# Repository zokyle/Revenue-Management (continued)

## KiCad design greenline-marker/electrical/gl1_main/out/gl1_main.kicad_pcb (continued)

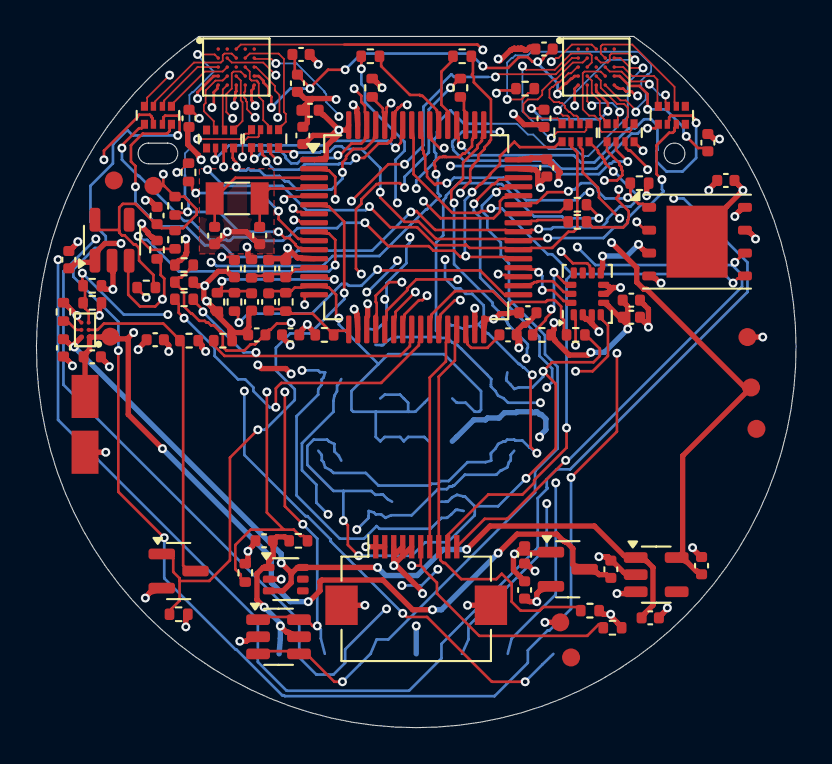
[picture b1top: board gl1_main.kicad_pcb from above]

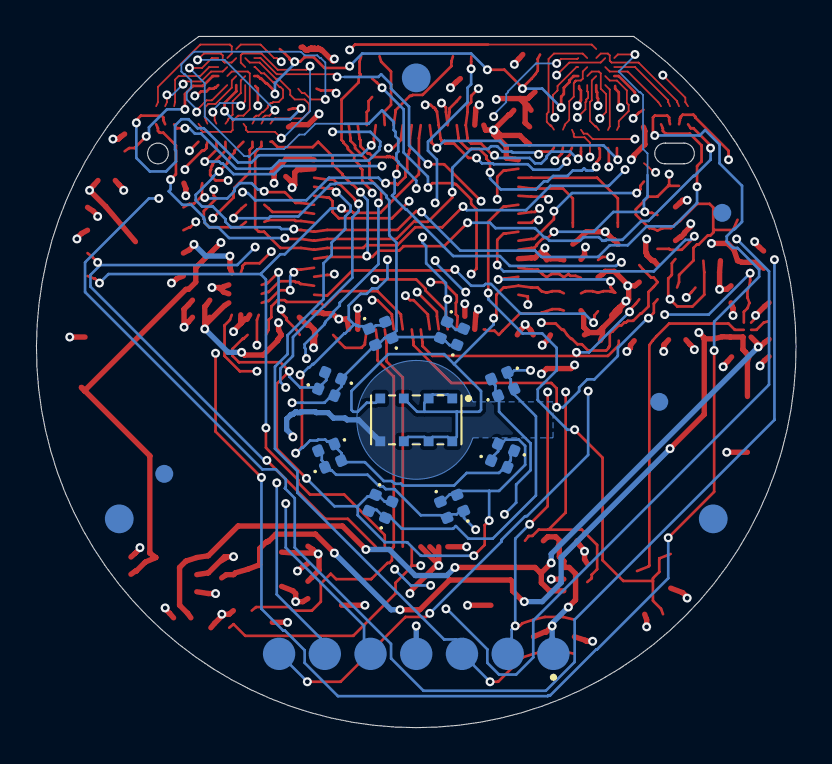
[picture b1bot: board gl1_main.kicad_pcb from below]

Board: 4 copper layers, 42.2 x 38.4 mm, 122 parts (24 on the bottom side), 95 nets.

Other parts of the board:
FID1, FID2, FID3, FID4, FID5, FID6: Fiducial; Fiducial_1mm_Mask2mm
FL1, FL2, FL3: Ball-foot land; BallFootLand_D1.6mm
H1: NPTH 1.15mm; NPTH_1.15mm

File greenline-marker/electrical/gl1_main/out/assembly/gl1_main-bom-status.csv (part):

Item,Qty,References,Value,Description,Footprint,MPN,Manufacturer,Distributor,Distributor PN,Unit Price,DNP,Status,Status note,Sourcing risk (docs/sourcing.csv),Approved alternates (docs/sourcing.csv),Sourcing row / status / checked on
1,16,C1 C2 C3 C4 C9 C10 C13 C14 C15 C17 C18 C28 C29 C30 C31 C34,100n,MLCC 0402 100 nF 16 V X7R,Capacitor_SMD:C_0402_1005Metric,GRM155R71C104KA88D,Murata,Digi-Key,490-3261-1-ND,,,PROVISIONAL,"MPN from memory, Digi-Key code from docs/SOURCING.md A17; the sourcing report records a conflicting not-recommended-for-new-designs flag","medium: stock is deep, but the life-cycle flag conflicts (not recommended for new designs at Octopart, IBS and LCSC; Active at Arrow and Future; Murata's own page not seen), and the part sits in 17 places on the two boards","Samsung CL05B104KO5NNNC (same value, voltage, dielectric and size): VERIFIED, own row",main-01 / VERIFIED / 2026-11-13
2,2,C5 C6,4u7,MLCC 0402 4.7 uF 6.3 V X5R,Capacitor_SMD:C_0402_1005Metric,GRM155R60J475ME47D,Murata,any authorised distributor (order by MPN),GRM155R60J475ME47D,,,PROVISIONAL,MPN from memory; value per DESIGN_SPEC / NETLIST_NOTES,low,"Samsung CL05A475MQ5NRNC: VERIFIED, own row",main-02 / VERIFIED / 2026-11-13
3,8,C7 C16 C19 C20 C21 C24 C25 C32,1u,MLCC 0402 1 uF 10 V X5R,Capacitor_SMD:C_0402_1005Metric,CL05A105KP5NNNC,Samsung Electro-Mechanics,any authorised distributor (order by MPN),CL05A105KP5NNNC,,,PROVISIONAL,MPN per docs/SOURCING.md action A1 (replaces the obsolete GRM155R61A105KE15D); DC-bias curve not read (A3),low,"Murata GRM155R61C105KA12D, 16 V (PROVISIONAL, own row)",replaces main-03 / VERIFIED / 2026-11-13
4,1,C8,10n,MLCC 0402 10 nF 50 V X7R,Capacitor_SMD:C_0402_1005Metric,GRM155R71H103KA88D,Murata,any authorised distributor (order by MPN),GRM155R71H103KA88D,,,PROVISIONAL,MPN from memory; value per DESIGN_SPEC / NETLIST_NOTES,low,"Samsung CL05B103KB5NNNC: VERIFIED, own row",main-04 / VERIFIED / 2026-11-13
5,2,C11 C12,6p8,MLCC 0402 6.8 pF 50 V C0G +-0.25 pF,Capacitor_SMD:C_0402_1005Metric,GRM1555C1H6R8CA01D,Murata,any authorised distributor (order by MPN),GRM1555C1H6R8CA01D,,,PROVISIONAL,MPN from memory; value per DESIGN_SPEC / NETLIST_NOTES,"low: a listing was seen, the quantity on hand was not","Yageo CC0402CRNPO9BN6R8 or KEMET C0402C689C5GACTU: both VERIFIED, own rows. Samsung CL05C6R8CB5NNNC: NOT FOUND on seven US distributor sites, do not list it",main-05 / VERIFIED / 2026-11-13
6,4,C22 C23 C26 C27,2u2,MLCC 0402 2.2 uF 10 V X5R,Capacitor_SMD:C_0402_1005Metric,GRM155R61A225KE01D,Murata,any authorised distributor (order by MPN),GRM155R61A225KE01D,,,PROVISIONAL,"MPN per docs/SOURCING.md action A2 (replaces GRM155R61A225KE95D, being discontinued; that KE01D is Murata's successor is the report's inference); DC-bias curve not read (A3)",medium: the exact reel code was out of stock at DigiKey in the one entry that was read,"Samsung CL05A225KP5NSNC (VERIFIED, own row); Murata GRT155R61A225KE01D (PROVISIONAL, own row)",replaces main-06 / VERIFIED / 2026-11-13
7,1,C33,10p,MLCC 0402 10 pF 50 V C0G 5 %,Capacitor_SMD:C_0402_1005Metric,GRM1555C1H100JA01D,Murata,any authorised distributor (order by MPN),GRM1555C1H100JA01D,,,PROVISIONAL,MPN from memory; value per DESIGN_SPEC / NETLIST_NOTES,low,"Samsung CL05C100JB5NNNC: VERIFIED, own row. Murata GRM1555C1H100FA01D (1 %) is DigiKey's suggested upgrade (not checked)",main-07 / VERIFIED / 2026-11-13
8,8,D1 D3 D5 D7 D9 D11 D13 D15,LED red,LED super red 631 nm 0402,LED_SMD:LED_0402_1005Metric,VLMS1500-GS08,Vishay,any authorised distributor (order by MPN),VLMS1500-GS08,,,PROVISIONAL,"MPN research-confirmed; land pattern is the generic KiCad 0402 LED, polarity mark and pad sizes not checked","low: a common part. 1000 markers need 8,000, more than the DigiKey figure; Mouser's covers it","Kingbright APHHS1005SURCK (carried from rev 2, not searched today: PROVISIONAL)",main-08 / VERIFIED / 2026-11-13
9,8,D2 D4 D6 D8 D10 D12 D14 D16,LED NIR,LED 850 nm 0402 (alternative: Inolux IN-S42CTQIR),LED_SMD:LED_0402_1005Metric,SFH 4053B,ams OSRAM,any authorised distributor (order by MPN),SFH 4053B,,,PROVISIONAL,"MPN from DESIGN_SPEC E3 (successor of the SFH 4053; its data sheet has not been read); land pattern is the generic KiCad 0402 LED, polarity mark and pad sizes not checked","medium to high: one US distributor with stock, and the life-cycle evidence conflicts (maker's page: full production; RS: 'currently unavailable' and 'being discontinued by the manufacturer')","Inolux IN-S42CTQIR, the alternative named in the design: VERIFIED at DigiKey, own row; dimmer (5.5 against 9 mW/sr typical at 70 mA)",main-09 / VERIFIED / 2026-11-13
10,1,J1,LCD FPC 10,"FPC connector 10 x 0.5 mm, TOP contact, 2.0 mm high; PIN-1 EDGE OF THE TAIL PROVISIONAL (tail pin n on pad 11 - n)",Connector_FFC-FPC:Hirose_FH12-10S-0.5SH_1x10-1MP_P0.50mm_Horizontal,FH12A-10S-0.5SH(55),Hirose,Digi-Key,HFK110CT-ND,,,PROVISIONAL,"top-contact FH12A on the bottom-contact FH12 land pattern (spec); pin order and pin-1 edge of the tail PROVISIONAL (LCD_TAIL, LCD_TAIL_PIN1_EDGE); placed per spec E24 (mouth at y -17.30), which overrides the YAML point; Digi-Key PN from docs/sourcing.csv","low for supply. Design risk: the footprint named in the BOM is the bottom-contact FH12 land pattern, and no extract confirmed that the top-contact FH12A fits it","Same part at Future and Heilind. No drop-in from another maker was searched. Fallback named by amendment E24 if the fold of the display's tail does not fit: a 1.0 mm high back-flip connector about 3.5 mm deep, 'Hirose FH34SRJ-10S-0.5SH class' (not searched: PROVISIONAL; a shallower connector, so a different land pattern)",main-11 / VERIFIED / 2026-11-13
11,1,PD1,VEMD8080,"PIN photodiode 4.5 mm2, 350-1100 nm; LAND PATTERN PROVISIONAL",gleda:VEMD8080_4.8x2.5mm_PROVISIONAL,VEMD8080,Vishay,any authorised distributor (order by MPN),VEMD8080,,,PROVISIONAL,"package research-confirmed; pad layout and anode pad from public footprints, not the Vishay drawing (VEMD8080_PADS)",low,Sister part VEMD8081 (DigiKey link seen; fit not checked: PROVISIONAL),main-12 / VERIFIED / 2026-11-13
12,1,Q1,BSS138,"N-MOSFET 50 V, VGS(th) 1.5 V max, SOT-23 (pulls the charger's TS input low)",Package_TO_SOT_SMD:SOT-23,BSS138LT1G,onsemi,Digi-Key,product page 918376 (SKU not seen),,,PROVISIONAL,"part named in DESIGN_SPEC; order code from docs/sourcing.csv; pin order (G1 S2 D3), threshold and leakage from memory",low,Same part at Arrow and Mouser,main-13 / VERIFIED / 2026-11-13
13,1,R1,10R,Resistor 0402 1 % 10R,Resistor_SMD:R_0402_1005Metric,RC0402FR-0710RL,Yageo,any authorised distributor (order by MPN),RC0402FR-0710RL,,,PROVISIONAL,MPN from memory; value per DESIGN_SPEC / NETLIST_NOTES,"low: one per marker, several distributors",Panasonic ERJ-2RKF10R0X (a Mouser page title only: PROVISIONAL),main-14 / VERIFIED / 2026-11-13
14,2,R2 R19,10k,Resistor 0402 1 % 10k,Resistor_SMD:R_0402_1005Metric,RC0402FR-0710KL,Yageo,any authorised distributor (order by MPN),RC0402FR-0710KL,,,PROVISIONAL,MPN from memory; value per DESIGN_SPEC / NETLIST_NOTES,low,"Panasonic ERJ-2RKF1002X: VERIFIED, own row",main-15 / VERIFIED / 2026-11-13
15,11,R3 R10 R12 R13 R15 R16 R20 R21 R22 R29 R30,100k,Resistor 0402 1 % 100k,Resistor_SMD:R_0402_1005Metric,RC0402FR-07100KL,Yageo,any authorised distributor (order by MPN),RC0402FR-07100KL,,,PROVISIONAL,MPN from memory; value per DESIGN_SPEC / NETLIST_NOTES,low,"Panasonic ERJ-2RKF1003X: VERIFIED, own row",main-16 / VERIFIED / 2026-11-13
16,2,R4 R5,1k,Resistor 0402 1 % 1k,Resistor_SMD:R_0402_1005Metric,RC0402FR-071KL,Yageo,any authorised distributor (order by MPN),RC0402FR-071KL,,,PROVISIONAL,MPN from memory; value per DESIGN_SPEC / NETLIST_NOTES,low,"Panasonic ERJ-2RKF1001X (from memory, not searched: PROVISIONAL)",main-17 / VERIFIED / 2026-11-13
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
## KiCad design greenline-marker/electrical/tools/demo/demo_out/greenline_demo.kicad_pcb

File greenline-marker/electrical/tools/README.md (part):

# gleda - GreenLine scripted EDA toolchain

`gleda` turns a "netlist as code" design description (Python) into a verified
KiCad 7 board.  KiCad's own DRC is the judge; nothing is reported as passing
unless KiCad says so.

The flow, each step a module that can be used on its own:

```
design script (Python)  ->  checks  ->  board  ->  router  ->  zone fill + KiCad DRC
                                                                     |
                 schematic + netlist round trip   <-   outputs (Gerber, drill, BOM,
                                                       pick-and-place, renders, JSON)
```

This file documents the design model, the checks, footprints, the board
builder, the DRC runner, the **router**, the **outputs**, the **schematic
generator** and the **demo build**, each with its limits.  Two sections are
written to be read on their own: **[Quick start: authoring a new
design](#quick-start-authoring-a-new-design)** and
**[Limitations](#limitations)** (everything the toolchain does not do, in one
place).

```
tools/
  gleda/
    model.py       design description (pure Python, no pcbnew)
    coords.py      THE design <-> KiCad coordinate conversion
    geometry.py    outline paths/polygons, placed pads, courtyards (shapely)
    footprints.py  programmatic footprints + KiCad library wrappers
    checks.py      ERC-style and placement checks
    board.py       .kicad_pcb / .kicad_pro / .kicad_dru generation, routing
                   primitives in/out, via tenting
    drc.py         zone fill + KiCad DRC + report parser + pass/fail policy
    kicad_cli.py   kicad-cli wrapper, SVG export, SVG reader
    router.py      autorouter (escape stage, negotiated routing, end game,
                   cleanup, exact audit, plane-fill prediction)
    raster.py      routing grid and exact obstacle rasterisation
    _astar.py      A* search kernel (numba-compiled when numba is installed)
    routeplot.py   quick matplotlib picture of a routed design (debug aid)
    outputs.py     Gerbers, drill, pick-and-place, BOM, netlist / mechanical JSON,
                   renders, fab README + zip - each checked against the model
    schematic.py   KiCad 7 schematic (one sheet per group), PDF, netlist round trip
  demo/
    quickstart_board.py  the smallest complete design + the whole flow (start here)
    demo_design.py     the GreenLine DEMO board (stand-in for the real GL-1)
    build_demo.py      checks -> board -> route -> DRC -> outputs -> schematic
    demo_out/          everything the last demo build produced
  tests/           pytest suite (run it from tools/)
    mini_design.py     round 30 mm fixture (castellated module, cutout, notch, slot)
    dshape_design.py   GreenLine-shaped fixture (D outline, LQFP-64, two BGAs,
                       bottom LED ring + contact row, fine net class)
    proof_core.py      builds both, KiCad DRC, plots, orientation proof
    proof_out/         outputs of the last proof run
```

## Requirements

KiCad 7.0.x with its Python module.  Always use the system interpreter:

```
cd electrical/tools
/usr/bin/python3 -m pytest -q            # test suite (about 2 minutes)
/usr/bin/python3 -m pytest -q --runslow  # ... plus the demo build from nothing (5 to 6 minutes in all)
/usr/bin/python3 demo/build_demo.py      # the whole flow on the demo board, exit 0 only if
                                         # checks, routing, KiCad DRC and round trip all pass
/usr/bin/python3 tests/proof_core.py     # build + DRC + render both reference boards
/usr/bin/python3 -m gleda.drc out/board.kicad_pcb [--allow-unconnected]
```

`pdftoppm` / `pdfinfo` (poppler-utils) turn KiCad's PDF plots into PNGs; numba
makes the router usable on real boards.  No GUI is ever started and nothing
is downloaded.

## The whole flow in one script

```python
import sys; sys.path.insert(0, "electrical/tools")
from gleda import checks, board, router, drc, outputs, schematic

design = my_design()                                    # a gleda.model.Design, see below

checks.run_checks(design).raise_if_errors()             # ERC-style + placement checks
files = board.build_board(design, "out")                # .kicad_pcb / .kicad_pro / .kicad_dru
result = router.route(design)                           # RouteResult; .complete, .unrouted
board.apply_routing(files.pcb, result.tracks, result.vias, via_tenting=design.via_tenting)
res = drc.run_drc(files.pcb, json_path="out/drc.json")  # zone fill + KiCad DRC
drc.assert_clean(res)                                   # 0 errors, 0 unconnected - or DrcError
package = outputs.generate_outputs(design, files.pcb, "out", drc_result=res, vias=result.vias)
assert package.ok, package.problems                     # plotted data == design model
sch = schematic.generate_schematic(design, "out")       # <name>.kicad_sch + one sheet per group
schematic.export_pdf(sch.root, "out/schematic.pdf")
trip = schematic.round_trip(design, sch.root)           # KiCad's netlist vs the model
assert trip.ok, trip.problems
```

`demo/build_demo.py` is exactly this with reporting around it.

## Quick start: authoring a new design

A design is one Python function that returns a `gleda.model.Design`; a second
short function takes it through the flow.  **Start from
`demo/quickstart_board.py`**: 135 lines, one 16-ball 0.5 mm BGA with its
capacitor, a pull-up and a contact row on a 24 mm D-shaped board, every step
below in the order one writes it, and a `build(design, out)` function that is
the whole flow with honest exit codes.  The test suite runs it, so it works as
written:

```
cd electrical/tools
/usr/bin/python3 demo/quickstart_board.py /some/empty/dir     # about 10 s
#   gleda checks for quickstart: 0 error(s), 0 warning(s)
#   routed 16/16 connections (100.0 %) of 10 nets, 102 tracks, 16 vias, 126.6 mm, 0 audit violation(s)
#   KiCad DRC: 0 error(s), 0 unconnected, 0 warning(s)
#   outputs: 34 files, 0 problem(s) against the model
#   netlist round trip matches: 10 nets, 26 pads, 4 components, 4 unconnected pins
```

`demo/demo_design.py` and `demo/build_demo.py` are the same thing at the size
of the real board (100 parts), with stage reporting around it.

1. **Outline and rules.**  `Outline(PathShape.d_shape(r, flat_y))` (or
   `Circle`, `RoundedPolygon`, any line + arc `PathShape`), then
   `add_hole` / `add_npth_slot` / `add_cutout`.  `Design(name, outline,
   layers=4, rules=US_4L_STD, board_thickness=0.8)`; use `US_4L_FINE` (board
   minimums 0.09 / 0.09 mm) only if a fine-pitch BGA forces it.
2. **Net classes.**  `Default` (0.15 / 0.127) and `Power` (0.30 / 0.127)
   exist.  Add `d.add_netclass("Fine", track_width=0.09, clearance=0.09)` for
   the nets on the inner balls of a 0.5 mm BGA and **declare where it may be
   fine**: `d.add_fine_area("U2", margin=5.0)`.  Outside the fine areas those
   nets are routed and DRC-checked at the standard 0.15 / 0.127 mm.  Try this
   first; if the router cannot finish that way (it cannot on the demo board),
   remove the fine areas - the fine tracks may then run anywhere on those
   nets, the checks warn, the router widens what it can, and the fab README
   tells the fab to quote the whole board at 0.09 / 0.09 mm.
3. **Parts.**  `d.add(Part(ref, value, footprint, pins=..., mpn=...,
   manufacturer=..., distributor=..., distributor_pn=..., unit_price=...,
   x=..., y=..., rotation=..., side="top" | "bottom", height_mm=...,
   group="sheet name"))`.  `footprint` is a KiCad `"Lib:Name"` string or a
   generator from `gleda.footprints` (`bga`, `quad_package`, `two_pad`,
   `pad_row`, `test_pad`, `battery_tab`, `fpc_connector`,
   `castellated_module` ...).  `pins` maps pin name -> pad number(s) and
   electrical type.  Bare pads and tabs get `in_bom=False`.
4. **Nets.**  `d.net("NAME", "U1.PA5", "R3.1", netclass="Power")`; every pin
   must be on a net, be of type `nc` or be listed in `d.no_connect(...)`.
   Supplies fed from outside the netlist get `power_flag=True`.
5. **Planes, keep-outs, mechanics.**  `d.add_plane("GND", "In1.Cu")`,
   `d.add_plane("V2V8", "In2.Cu", routable=True)` (plane and third routing
   layer), `d.add_body_keepout("U4")` (no copper under a MEMS body),
   `d.add_keepout(shape, layers=..., tracks=..., vias=..., copper=...,
   footprints=...)` (for example `tracks=False, vias=True` over a wetted
   area: no via holes there), `d.add_placement_keepout`, `d.add_height_limit`.
6. **Fab and assembly details.**  `d.via_tenting = "bottom"`,
   `d.via_protection = "plugged from the bottom side (IPC-4761 type III-a)"`,
   `d.fab_notes.append("...")`, three `d.add_fiducial(x, y, side=...)` per
   assembled side.
7. **Run the checks until they are clean**: `print(checks.run_checks(d).text())`.
   Errors stop the flow; read the warnings (`fine_unconfined`, `no_fiducials`,
   `plane_partial`, `decoupling_far` ...).
8. **Build, route, judge, export** - the script under "The whole flow in one
   script" above.  The router's result is honest (`result.complete`,
   `result.unrouted`, `result.warnings`); KiCad's DRC decides
   (`drc.assert_clean`); `outputs.generate_outputs` refuses a board that is
   not clean and verifies what it plotted against the model.

What makes a board routable by THIS router (learned on the demo, see the end
of this file): pins of a fixed-function part on the side that faces their
destination; about 1.4 x 2.0 mm per 0402 that needs a plane via; the sides of
a BGA that face the rest of the circuit kept clear for the bus escape; nothing
in the pocket between a hole and the next part; fiducials and fine areas
placed before routing (both take routing room).

**The first mistake everybody makes**: an inner ball of a 0.5 mm-pitch BGA on
a net whose class is wider than 0.09 mm (`Default`, `Power`).  Only a 0.09 mm
track with 0.09 mm clearance passes between two 0.23 mm balls, a via does not
fit between them and vias are never put in pads - so such a ball cannot be
reached, whatever net it is on, GND included.  Put every net that touches an
inner ball into a fine class (the demo: `Fine` for signals, `CamPower`
0.15 / 0.09 for supply balls on the outer ring), give the BGA pads
`pad_clearance=0.09`, and keep supplies on the outer ring where the ball map
lets you.  The router does not hang on it and does not pretend:

```
routed 15/16 connections (93.8 %) of 10 nets, 83 tracks, 15 vias, ...
OPEN D0: [['J1.3'], ['U1.B2']]  [no path from U1.B2 to J1.3]
```

A net the router leaves open is always reported like this
(`result.unrouted` -> `Unrouted.net`, `.pieces`, `.reason`; per connection in
`result.failures`) and `result.complete` is False.  Move a part or a pin,
change the class, and run again - or route that net by hand in KiCad and mark
it `no_route=True`.

## Conventions (read this first)

* Units are millimetres.  The design origin is the **board centre** (for the
  D-shaped board: the centre of the circle), **+x is right, +y is up** as seen
  from the top of the board; rotation is counter-clockwise positive.
* KiCad's y axis points down.  The conversion happens in exactly one module,
  `gleda/coords.py` (`to_kicad_mm`, `from_kicad_mm`, ...).  The board centre is
  placed at (100, 100) mm on the KiCad page and the board's auxiliary
  (drill/place) origin is set to the same point.
* Footprint-local coordinates (custom footprints, `FootprintGeom`) use the
  same handedness: +y up, looking at the component side.
* **Bottom-side parts** follow KiCad's native definition, so `Part.rotation`
  is the number KiCad stores, shows and writes to position files:
  the footprint is flipped about its local X axis and then rotated CCW as
  seen from the top:

      top:     board = (x, y) + R(rotation) . (lx,  ly)
      bottom:  board = (x, y) + R(rotation) . (lx, -ly)

  `coords.local_to_board()` implements this and
  `tests/test_board.py::test_pads_match_model_geometry` proves that every pad
  position predicted by the model equals what pcbnew reports for the saved
  board.  `tests/test_board.py::test_top_view_svg_has_plus_y_up` proves from a
  KiCad SVG plot that a part placed at +y is drawn toward the top.

## Describing a design

```python
from gleda.model import (Design, Outline, Circle, RoundedPolygon, PathShape, Part,
                         two_pin, n_pin, US_4L_FINE, BOTTOM)
from gleda import footprints as F

# circle r = 21.2 mm about the origin, clipped by the chord y = +17.3 mm
outline = Outline(PathShape.d_shape(21.2, 17.3))
# also: Outline(Circle(0, 0, 19.0)), RoundedPolygon(...), any line + arc path:
#   PathShape.begin(-5, 0).line_to(5, 0).arc_to(-5, 0, 0, 0, ccw=True).close()
#   PathShape.clipped_circle(0, 0, 21.2, [(90, 17.3), (270, 19.0)])
outline.add_cutout(Circle(9.0, 0.0, 6.5))              # internal routed cutout
outline.add_notch(RoundedPolygon.rect(0, -21.2, 3, 2, 0.4))   # crosses the edge
outline.add_slot(-6, -11, -4, -11, 0.8)
outline.add_hole(-12, 5, 1.2)                          # NPTH

d = Design("greenline", outline, layers=4, rules=US_4L_FINE, board_thickness=0.8)
d.add_netclass("Fine", track_width=0.09, clearance=0.09)   # BGA escape only
d.via_tenting = "bottom"                               # "both" (default) | "bottom" | "top" | "none"
d.via_protection = "plugged from the bottom side (IPC-4761 type III-a)"   # -> fab README
d.fab_notes.append("The bottom side is a wetted surface: no open via holes there.")

cam = F.bga("Cam_BGA25", 5, 5, pitch=0.5, pad_d=0.23, body=(3.47, 2.95), height=2.76,
            pad_clearance=0.09, courtyard_margin=0.2)
d.add(Part("U2", "Camera", cam,
           pins={"D0": ("B2", "bidir"), "AVDD": ("C5", "power_in"),
                 "GND": (("E2", "E3", "E4"), "power_in"), "NC": ("A1", "nc")},  # ... all balls
           mpn="...", manufacturer="...", distributor="Digi-Key", distributor_pn="...",
           unit_price=6.0, x=-10.2, y=15.6, rotation=0, side="top", height_mm=2.76,
           group="camera"))
d.add(Part("C1", "100n", "Capacitor_SMD:C_0402_1005Metric", pins=two_pin(),
           mpn="...", x=-7.2, y=15.3, rotation=90, group="camera"))
d.add(Part("J2", "Cradle pads", F.pad_row("ContactRow", 7, 2.54, 1.8), pins=n_pin(7),
           x=0, y=-17.0, side=BOTTOM, in_bom=False))    # bare pads on the bottom

d.net("GND", "U2.GND", "C1.2", "J2.4", netclass="Power")
d.net("V2V8", "U2.AVDD", "C1.1", netclass="Power", power_flag=True)
d.net("CAM_D0", "U2.D0", "U1.PC6", netclass="Fine")    # inner ball: fine class
d.no_connect("U1.P0.13")                               # pin names may contain dots

d.add_plane("GND", "In1.Cu")
d.add_plane("+3V0", "In2.Cu")
d.add_body_keepout("U4")                               # no copper on F.Cu under the IMU body
d.add_keepout(RoundedPolygon.rect(0, -5.2, 34, 10), layers=("F.Cu",), name="battery",
              tracks=False, vias=False, copper=False, footprints=True)   # placement only
d.add_fine_area("U2", margin=5.0)                      # Fine may be fine only around U2
d.add_fiducial(-19.3, -0.8)                            # FID1, top; three per assembled side
d.add_fiducial(-13.5, -3.0, side=BOTTOM)
```

Pin shorthand accepted by `Part(pins=...)`: `"5"`, `("5", "input")`,
`(("6", "7"), "power_in")`, `["6", "7"]` or a `Pin` object.  Electrical types:
`power_in, power_out, passive, input, output, bidir, open_drain, nc`.
`pins=None` means a two-pin passive (`two_pin()`).

Per-net router options live on `Net`: `width`, `max_vias`, `layers`,
`no_route`, `priority`; `power_flag=True` marks a supply that is driven from
outside the netlist (battery tab, connector).

Tri-state outputs that share a line (camera bus, SPI MISO) must be typed
`bidir`: two `output` pins on one net are an `output_conflict` error.

### Rule set

`gleda.model.Rules` is a frozen parameter object; the default instance is
`US_4L_STD`:

| rule | `US_4L_STD` | `US_4L_FINE` |
|------|-------------|--------------|
| board minimum track / clearance | 0.127 mm / 0.127 mm | **0.09 mm / 0.09 mm** |
| via (through only) | 0.50 mm pad / 0.25 mm drill | same |
| min annular ring | 0.125 mm | same |
| hole to hole | 0.25 mm | same |
| hole wall to foreign copper | 0.20 mm | same |
| copper to board edge | 0.30 mm | same |
| default / power track | 0.15 mm / 0.30 mm | same |
| default clearance (classes Default, Power) | 0.127 mm | same |
| zone clearance / min width | 0.20 mm / 0.15 mm | same |

Use `dataclasses.replace(US_4L_STD, name="...", ...)` for another fab and pass
it to `Design(rules=...)`.

### Net classes: own track width and clearance

`Design` creates `Default` (0.15 / 0.127) and `Power` (0.30 / 0.127) from the
rules; `Design.add_netclass(name, track_width, clearance, via_diameter,
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
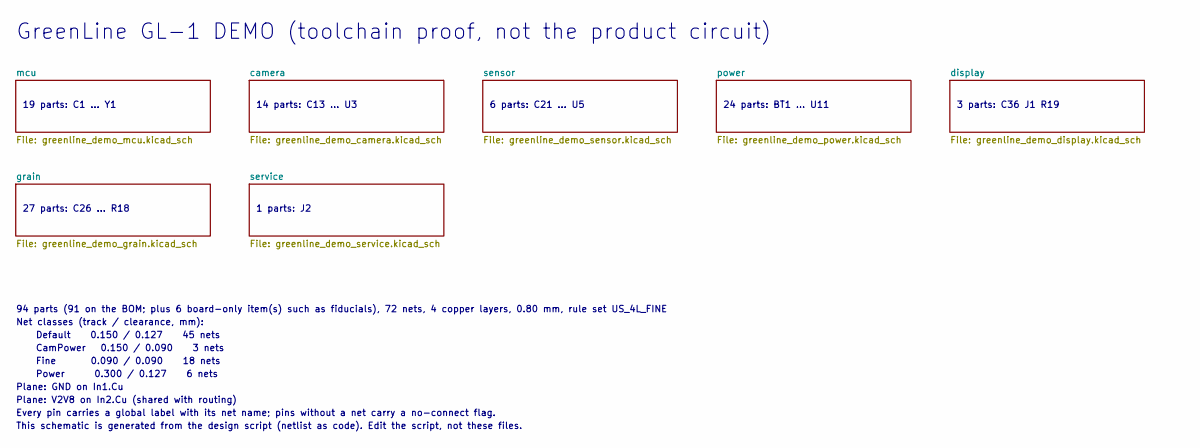
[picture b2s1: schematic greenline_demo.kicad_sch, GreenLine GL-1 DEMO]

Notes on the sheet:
GreenLine GL-1 DEMO (toolchain proof, not the product circuit)
19 parts: C1 ... Y1
14 parts: C13 ... U3
6 parts: C21 ... U5
24 parts: BT1 ... U11
3 parts: C36 J1 R19
27 parts: C26 ... R18
1 parts: J2
94 parts (91 on the BOM; plus 6 board-only item(s) such as fiducials), 72 nets, 4 copper layers, 0.80 mm, rule set US_4L_FINE
Net classes (track / clearance, mm):
Default 0.150 / 0.127 45 nets
CamPower 0.150 / 0.090 3 nets
Fine 0.090 / 0.090 18 nets
Power 0.300 / 0.127 6 nets
Plane: GND on In1.Cu
Plane: V2V8 on In2.Cu (shared with routing)
Every pin carries a global label with its net name; pins without a net carry a no-connect flag.
This schematic is generated from the design script (netlist as code). Edit the script, not these files.

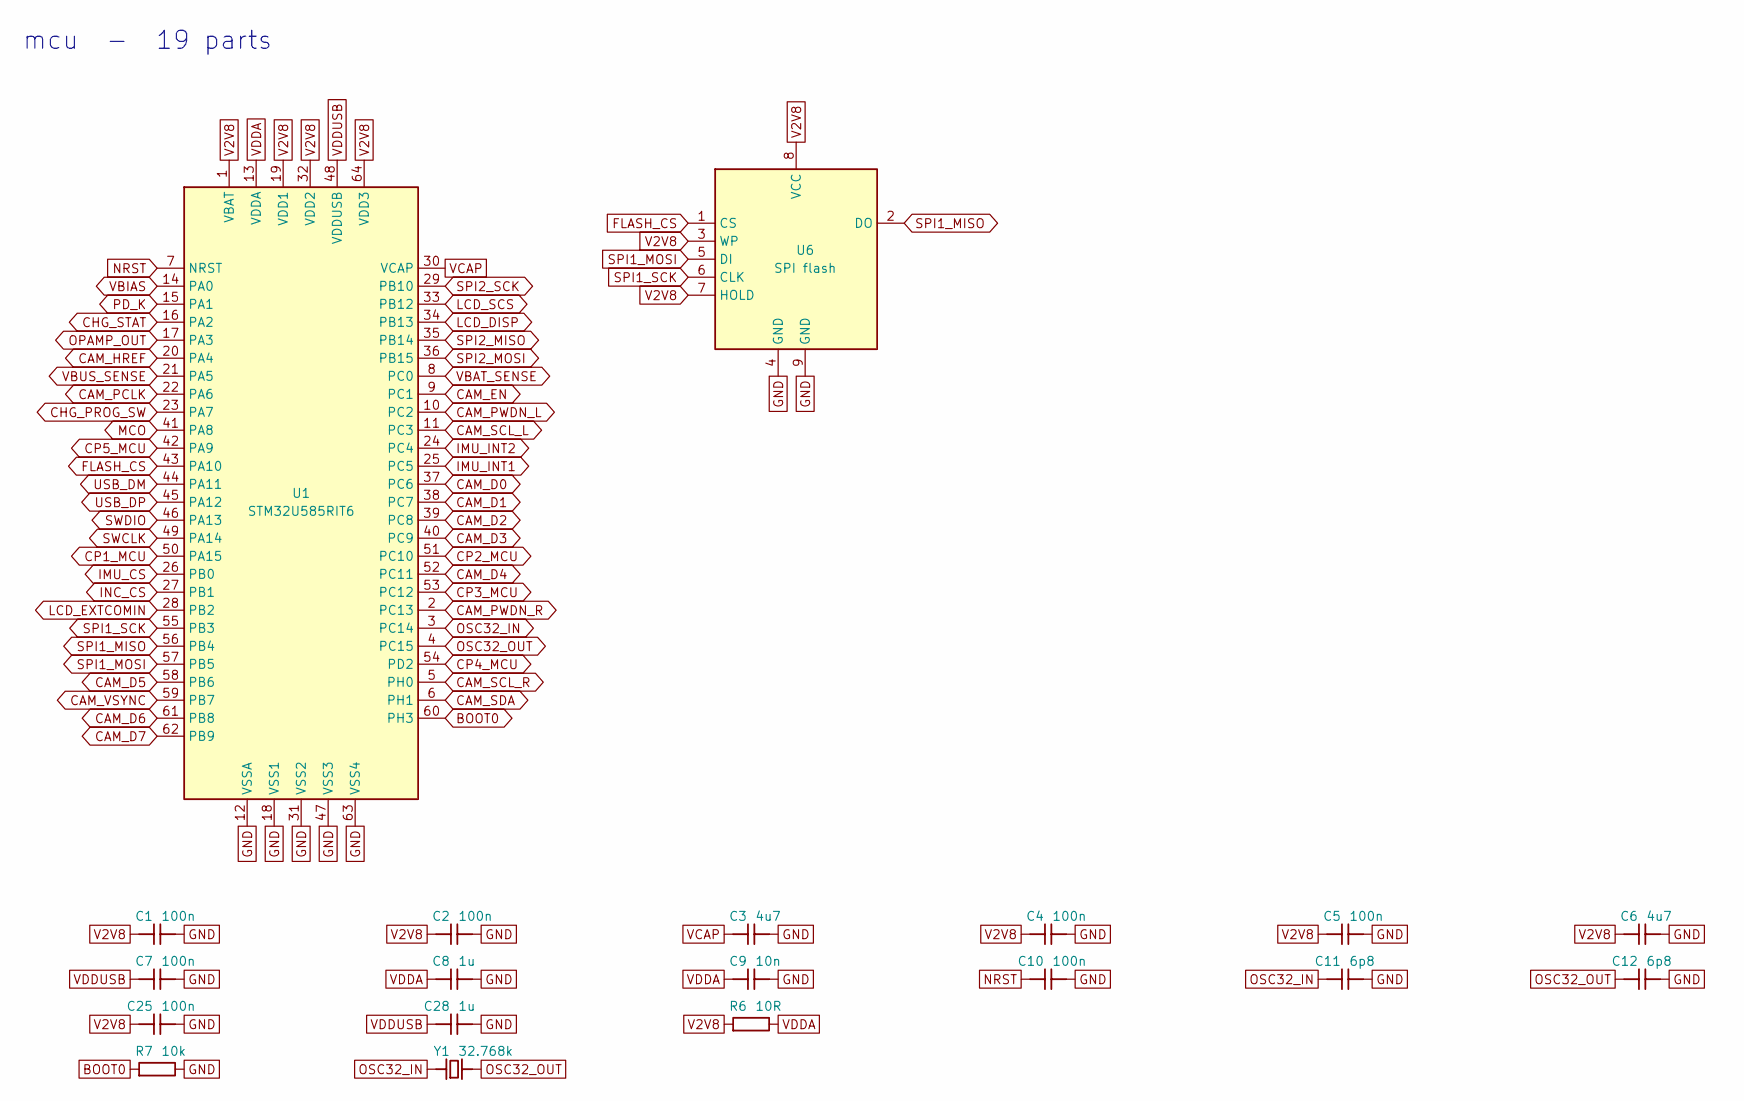
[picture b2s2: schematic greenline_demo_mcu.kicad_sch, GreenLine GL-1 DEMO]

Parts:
C1, C2, C4, C5, C7, C10, C25: 100n; C_0402_1005Metric; MPN GRM155R71C104KA88D
C3, C6: 4u7; C_0402_1005Metric; MPN GRM155R60J475ME47D
C8, C28: 1u; C_0402_1005Metric; MPN GRM155R61A105KE15D
C9: 10n; C_0402_1005Metric; MPN GRM155R71H103KA88D
C11, C12: 6p8; C_0402_1005Metric; MPN GRM1555C1H6R8CA01D
R6: 10R; R_0402_1005Metric; MPN RC0402FR-0710RL
R7: 10k; R_0402_1005Metric; MPN RC0402FR-0710KL
U1: STM32U585RIT6; LQFP-64_10x10mm_P0.5mm; MPN STM32U585RIT6
U6: SPI flash; WSON-8-1EP_6x5mm_P1.27mm_EP3.4x4.3mm; MPN MX25R6435FZNIL0
Y1: 32.768k; Crystal_SMD_3215-2Pin_3.2x1.5mm; MPN ABS07-120-32.768KHZ-T

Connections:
BOOT0: R7.1, U1.60 (PH3)
CAM_D0: U1.37 (PC6); also elsewhere on the board
CAM_D1: U1.38 (PC7); also elsewhere on the board
CAM_D2: U1.39 (PC8); also elsewhere on the board
CAM_D3: U1.40 (PC9); also elsewhere on the board
CAM_D4: U1.52 (PC11); also elsewhere on the board
CAM_D5: U1.58 (PB6); also elsewhere on the board
CAM_D6: U1.61 (PB8); also elsewhere on the board
CAM_D7: U1.62 (PB9); also elsewhere on the board
CAM_EN: U1.9 (PC1); also elsewhere on the board
CAM_HREF: U1.20 (PA4); also elsewhere on the board
CAM_PCLK: U1.22 (PA6); also elsewhere on the board
CAM_PWDN_L: U1.10 (PC2); also elsewhere on the board
CAM_PWDN_R: U1.2 (PC13); also elsewhere on the board
CAM_SCL_L: U1.11 (PC3); also elsewhere on the board
CAM_SCL_R: U1.5 (PH0); also elsewhere on the board
CAM_SDA: U1.6 (PH1); also elsewhere on the board
CAM_VSYNC: U1.59 (PB7); also elsewhere on the board
CHG_PROG_SW: U1.23 (PA7); also elsewhere on the board
CHG_STAT: U1.16 (PA2); also elsewhere on the board
CP1_MCU: U1.50 (PA15); also elsewhere on the board
CP2_MCU: U1.51 (PC10); also elsewhere on the board
CP3_MCU: U1.53 (PC12); also elsewhere on the board
CP4_MCU: U1.54 (PD2); also elsewhere on the board
CP5_MCU: U1.42 (PA9); also elsewhere on the board
FLASH_CS: U1.43 (PA10), U6.1 (CS)
GND: C1.2, C2.2, C3.2, C4.2, C5.2, C6.2, C7.2, C8.2, C9.2, C10.2, C11.2, C12.2, C25.2, C28.2, R7.2, U1.12 (VSSA), U1.18 (VSS1), U1.31 (VSS2), U1.47 (VSS3), U1.63 (VSS4), U6.4 (GND), U6.9 (GND); also elsewhere on the board
IMU_CS: U1.26 (PB0); also elsewhere on the board
IMU_INT1: U1.25 (PC5); also elsewhere on the board
IMU_INT2: U1.24 (PC4); also elsewhere on the board
INC_CS: U1.27 (PB1); also elsewhere on the board
LCD_DISP: U1.34 (PB13); also elsewhere on the board
LCD_EXTCOMIN: U1.28 (PB2); also elsewhere on the board
LCD_SCS: U1.33 (PB12); also elsewhere on the board
MCO: U1.41 (PA8); also elsewhere on the board
NRST: C10.1, U1.7 (NRST); also elsewhere on the board
OPAMP_OUT: U1.17 (PA3); also elsewhere on the board
OSC32_IN: C11.1, U1.3 (PC14), Y1.1
OSC32_OUT: C12.1, U1.4 (PC15), Y1.2
PD_K: U1.15 (PA1); also elsewhere on the board
SPI1_MISO: U1.56 (PB4), U6.2 (DO)
SPI1_MOSI: U1.57 (PB5), U6.5 (DI); also elsewhere on the board
SPI1_SCK: U1.55 (PB3), U6.6 (CLK); also elsewhere on the board
SPI2_MISO: U1.35 (PB14); also elsewhere on the board
SPI2_MOSI: U1.36 (PB15); also elsewhere on the board
SPI2_SCK: U1.29 (PB10); also elsewhere on the board
SWCLK: U1.49 (PA14); also elsewhere on the board
SWDIO: U1.46 (PA13); also elsewhere on the board
USB_DM: U1.44 (PA11); also elsewhere on the board
USB_DP: U1.45 (PA12); also elsewhere on the board
V2V8: C1.1, C2.1, C4.1, C5.1, C6.1, C25.1, R6.1, U1.1 (VBAT), U1.19 (VDD1), U1.32 (VDD2), U1.64 (VDD3), U6.3 (WP), U6.7 (HOLD), U6.8 (VCC); also elsewhere on the board
VBAT_SENSE: U1.8 (PC0); also elsewhere on the board
VBIAS: U1.14 (PA0); also elsewhere on the board
VBUS_SENSE: U1.21 (PA5); also elsewhere on the board
VCAP: C3.1, U1.30 (VCAP)
VDDA: C8.1, C9.1, R6.2, U1.13 (VDDA)
VDDUSB: C7.1, C28.1, U1.48 (VDDUSB); also elsewhere on the board

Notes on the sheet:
mcu - 19 parts

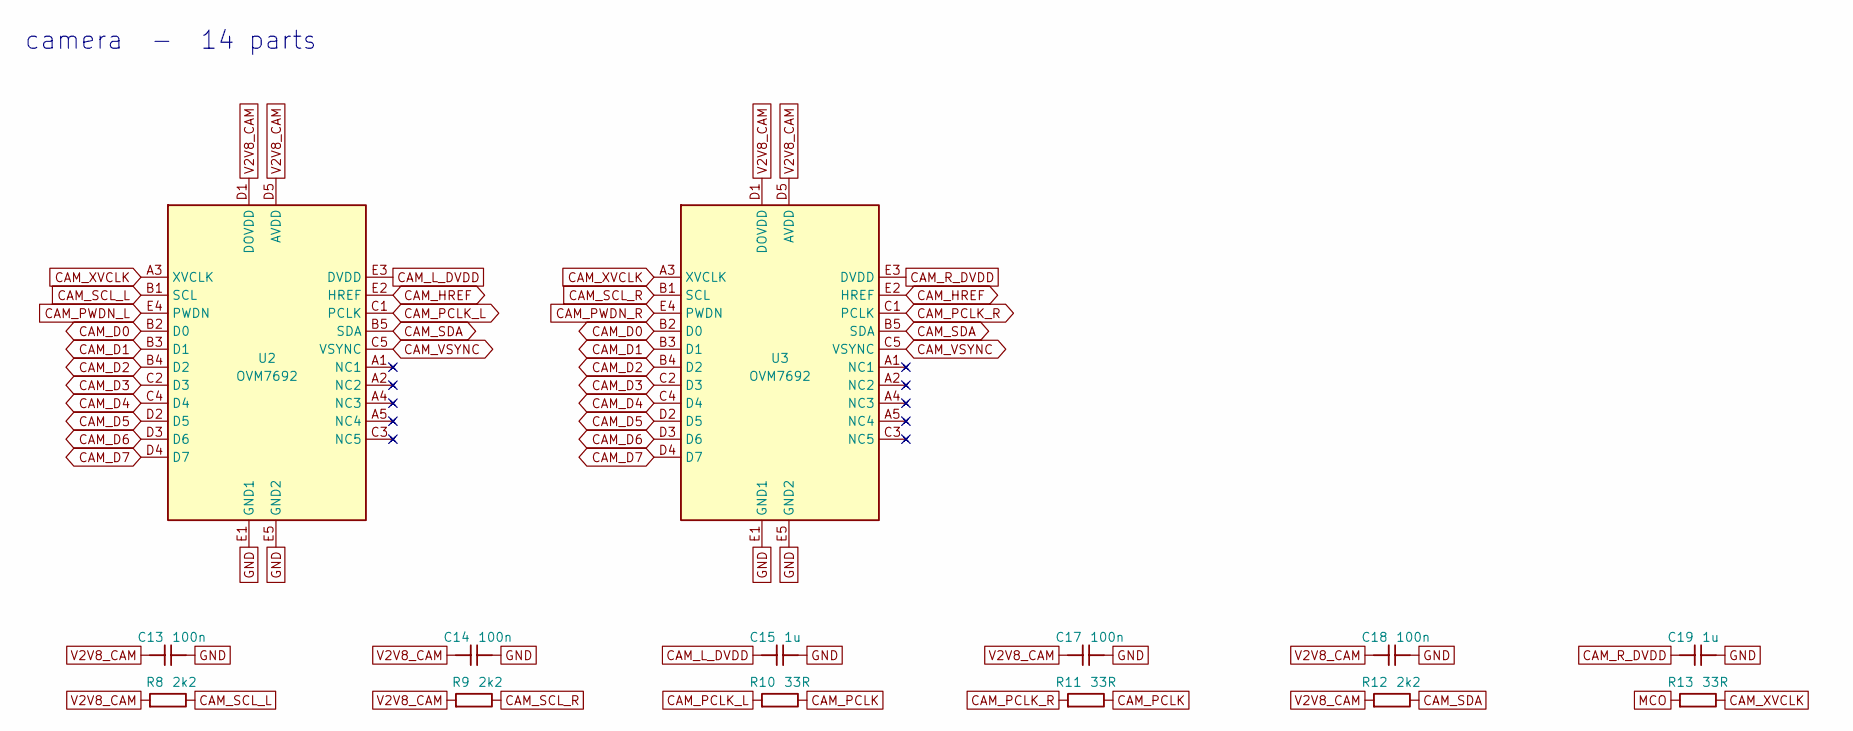
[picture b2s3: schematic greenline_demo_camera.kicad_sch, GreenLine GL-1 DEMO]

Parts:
C13, C14, C17, C18: 100n; C_0402_1005Metric; MPN GRM155R71C104KA88D
C15, C19: 1u; C_0402_1005Metric; MPN GRM155R61A105KE15D
R8, R9, R12: 2k2; R_0402_1005Metric; MPN RC0402FR-072K2L
R10, R11, R13: 33R; R_0402_1005Metric; MPN RC0402FR-0733RL
U2, U3: OVM7692; CamCube_BGA25_P0.5; MPN OVM7692-RYAA

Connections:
CAM_D0: U2.B2 (D0), U3.B2 (D0); also elsewhere on the board
CAM_D1: U2.B3 (D1), U3.B3 (D1); also elsewhere on the board
CAM_D2: U2.B4 (D2), U3.B4 (D2); also elsewhere on the board
CAM_D3: U2.C2 (D3), U3.C2 (D3); also elsewhere on the board
CAM_D4: U2.C4 (D4), U3.C4 (D4); also elsewhere on the board
CAM_D5: U2.D2 (D5), U3.D2 (D5); also elsewhere on the board
CAM_D6: U2.D3 (D6), U3.D3 (D6); also elsewhere on the board
CAM_D7: U2.D4 (D7), U3.D4 (D7); also elsewhere on the board
CAM_HREF: U2.E2 (HREF), U3.E2 (HREF); also elsewhere on the board
CAM_L_DVDD: C15.1, U2.E3 (DVDD)
CAM_PCLK: R10.2, R11.2; also elsewhere on the board
CAM_PCLK_L: R10.1, U2.C1 (PCLK)
CAM_PCLK_R: R11.1, U3.C1 (PCLK)
CAM_PWDN_L: U2.E4 (PWDN); also elsewhere on the board
CAM_PWDN_R: U3.E4 (PWDN); also elsewhere on the board
CAM_R_DVDD: C19.1, U3.E3 (DVDD)
CAM_SCL_L: R8.2, U2.B1 (SCL); also elsewhere on the board
CAM_SCL_R: R9.2, U3.B1 (SCL); also elsewhere on the board
CAM_SDA: R12.2, U2.B5 (SDA), U3.B5 (SDA); also elsewhere on the board
CAM_VSYNC: U2.C5 (VSYNC), U3.C5 (VSYNC); also elsewhere on the board
CAM_XVCLK: R13.2, U2.A3 (XVCLK), U3.A3 (XVCLK)
GND: C13.2, C14.2, C15.2, C17.2, C18.2, C19.2, U2.E1 (GND1), U2.E5 (GND2), U3.E1 (GND1), U3.E5 (GND2); also elsewhere on the board
MCO: R13.1; also elsewhere on the board
V2V8_CAM: C13.1, C14.1, C17.1, C18.1, R8.1, R9.1, R12.1, U2.D1 (DOVDD), U2.D5 (AVDD), U3.D1 (DOVDD), U3.D5 (AVDD); also elsewhere on the board

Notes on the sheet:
camera - 14 parts

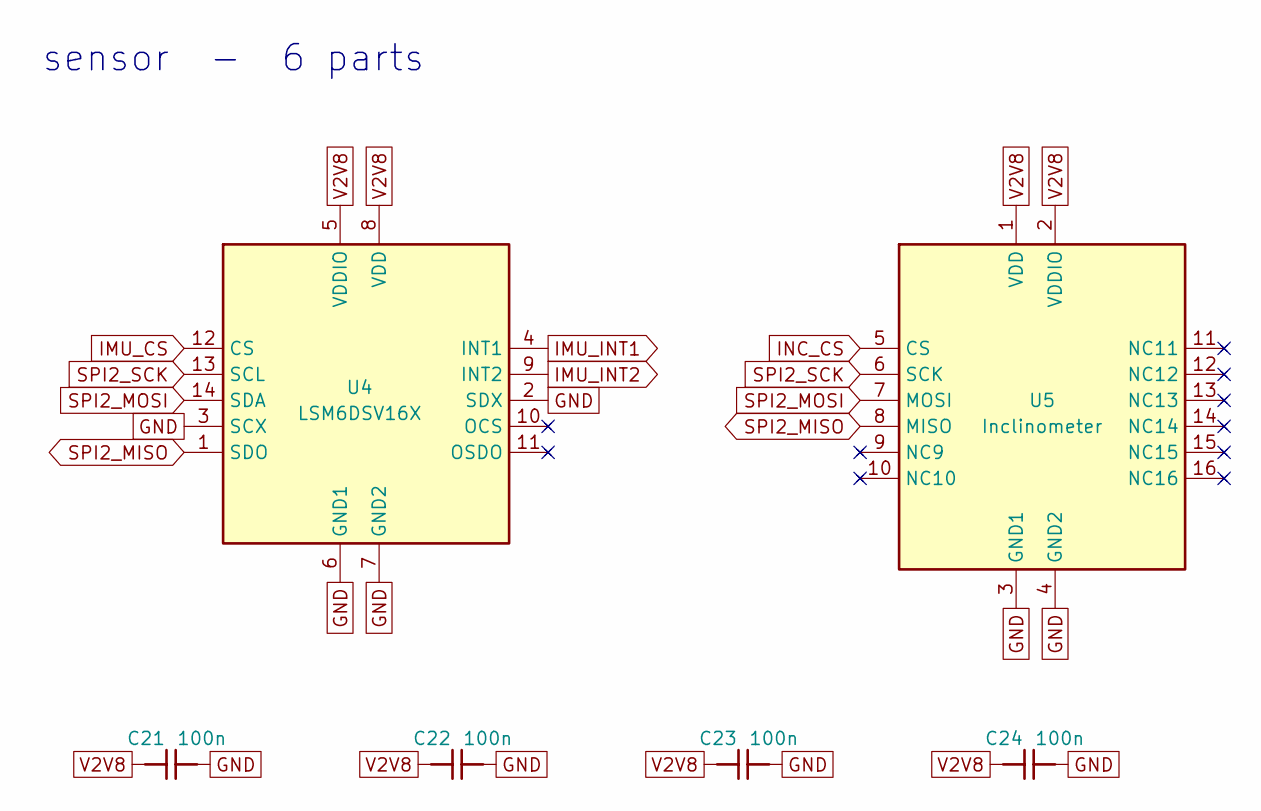
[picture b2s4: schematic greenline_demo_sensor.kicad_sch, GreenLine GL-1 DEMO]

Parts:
C21, C22, C23, C24: 100n; C_0402_1005Metric; MPN GRM155R71C104KA88D
U4: LSM6DSV16X; LGA-14_3x2.5mm_P0.5mm_LayoutBorder3x4y; MPN LSM6DSV16XTR
U5: Inclinometer; LGA-16_5x5mm_P1.0mm; MPN IIS2ICLXTR

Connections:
GND: C21.2, C22.2, C23.2, C24.2, U4.2 (SDX), U4.3 (SCX), U4.6 (GND1), U4.7 (GND2), U5.3 (GND1), U5.4 (GND2); also elsewhere on the board
IMU_CS: U4.12 (CS); also elsewhere on the board
IMU_INT1: U4.4 (INT1); also elsewhere on the board
IMU_INT2: U4.9 (INT2); also elsewhere on the board
INC_CS: U5.5 (CS); also elsewhere on the board
SPI2_MISO: U4.1 (SDO), U5.8 (MISO); also elsewhere on the board
SPI2_MOSI: U4.14 (SDA), U5.7 (MOSI); also elsewhere on the board
SPI2_SCK: U4.13 (SCL), U5.6 (SCK); also elsewhere on the board
V2V8: C21.1, C22.1, C23.1, C24.1, U4.5 (VDDIO), U4.8 (VDD), U5.1 (VDD), U5.2 (VDDIO); also elsewhere on the board

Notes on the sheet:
sensor - 6 parts

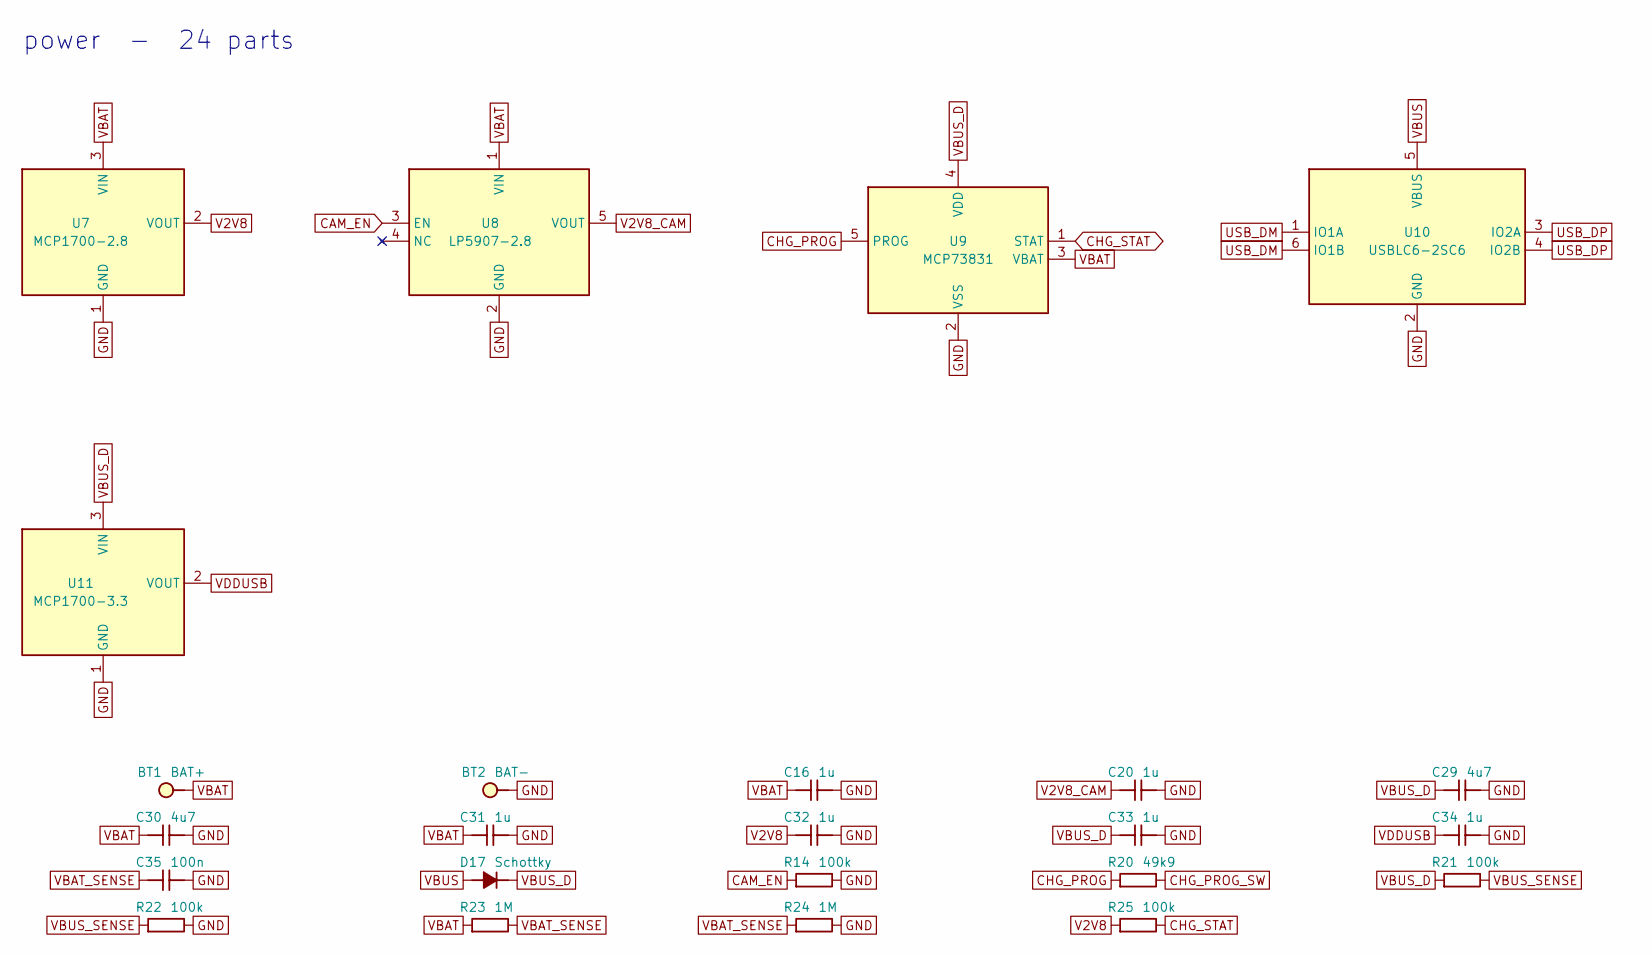
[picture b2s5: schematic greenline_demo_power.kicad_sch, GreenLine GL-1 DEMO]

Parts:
BT1: BAT+; BatteryTab_1.2x2mm
BT2: BAT-; BatteryTab_1.2x2mm
C16, C20, C31, C32, C33, C34: 1u; C_0402_1005Metric; MPN GRM155R61A105KE15D
C29, C30: 4u7; C_0402_1005Metric; MPN GRM155R60J475ME47D
C35: 100n; C_0402_1005Metric; MPN GRM155R71C104KA88D
D17: Schottky; D_SOD-323; MPN BAT60JFILM
R14, R21, R22, R25: 100k; R_0402_1005Metric; MPN RC0402FR-07100KL
R20: 49k9; R_0402_1005Metric; MPN RC0402FR-0749K9L
R23, R24: 1M; R_0402_1005Metric; MPN RC0402FR-071ML
U7: MCP1700-2.8; SOT-23; MPN MCP1700T-2802E/TT
U8: LP5907-2.8; SOT-23-5; MPN LP5907MFX-2.8/NOPB
U9: MCP73831; SOT-23-5; MPN MCP73831T-2ACI/OT
U10: USBLC6-2SC6; SOT-23-6; MPN USBLC6-2SC6
U11: MCP1700-3.3; SOT-23; MPN MCP1700T-3302E/TT

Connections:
CAM_EN: R14.1, U8.3 (EN); also elsewhere on the board
CHG_PROG: R20.1, U9.5 (PROG)
CHG_PROG_SW: R20.2; also elsewhere on the board
CHG_STAT: R25.2, U9.1 (STAT); also elsewhere on the board
GND: BT2.1, C16.2, C20.2, C29.2, C30.2, C31.2, C32.2, C33.2, C34.2, C35.2, R14.2, R22.2, R24.2, U7.1 (GND), U8.2 (GND), U9.2 (VSS), U10.2 (GND), U11.1 (GND); also elsewhere on the board
USB_DM: U10.1 (IO1A), U10.6 (IO1B); also elsewhere on the board
USB_DP: U10.3 (IO2A), U10.4 (IO2B); also elsewhere on the board
V2V8: C32.1, R25.1, U7.2 (VOUT); also elsewhere on the board
V2V8_CAM: C20.1, U8.5 (VOUT); also elsewhere on the board
VBAT: BT1.1, C16.1, C30.1, C31.1, R23.1, U7.3 (VIN), U8.1 (VIN), U9.3 (VBAT)
VBAT_SENSE: C35.1, R23.2, R24.1; also elsewhere on the board
VBUS: D17.2 (A), U10.5 (VBUS); also elsewhere on the board
VBUS_D: C29.1, C33.1, D17.1 (K), R21.1, U9.4 (VDD), U11.3 (VIN)
VBUS_SENSE: R21.2, R22.1; also elsewhere on the board
VDDUSB: C34.1, U11.2 (VOUT); also elsewhere on the board

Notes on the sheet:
power - 24 parts

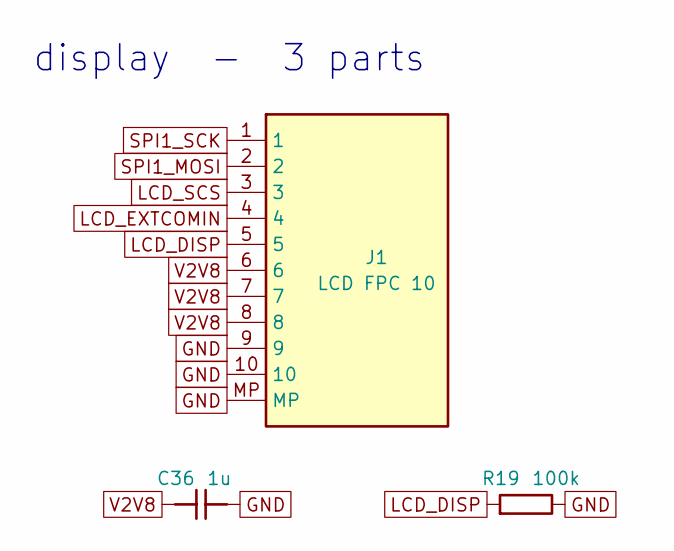
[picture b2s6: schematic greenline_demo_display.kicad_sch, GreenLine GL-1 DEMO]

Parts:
C36: 1u; C_0402_1005Metric; MPN GRM155R61A105KE15D
J1: LCD FPC 10; Hirose_FH12-10S-0.5SH_1x10-1MP_P0.50mm_Horizontal; MPN FH12A-10S-0.5SH(55)
R19: 100k; R_0402_1005Metric; MPN RC0402FR-07100KL

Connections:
GND: C36.2, J1.9, J1.10, J1.MP, R19.2; also elsewhere on the board
LCD_DISP: J1.5, R19.1; also elsewhere on the board
LCD_EXTCOMIN: J1.4; also elsewhere on the board
LCD_SCS: J1.3; also elsewhere on the board
SPI1_MOSI: J1.2; also elsewhere on the board
SPI1_SCK: J1.1; also elsewhere on the board
V2V8: C36.1, J1.6, J1.7, J1.8; also elsewhere on the board

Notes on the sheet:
display - 3 parts

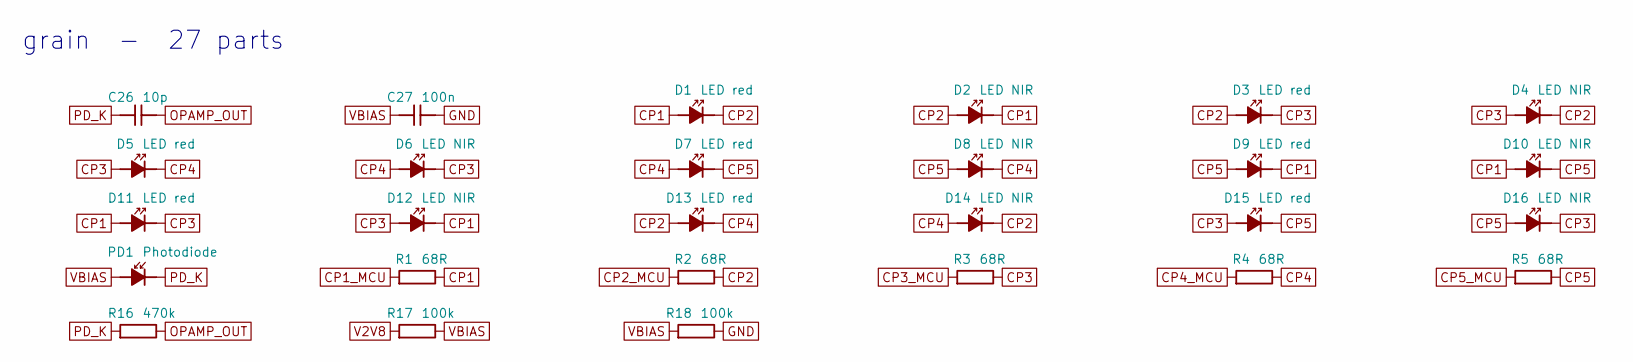
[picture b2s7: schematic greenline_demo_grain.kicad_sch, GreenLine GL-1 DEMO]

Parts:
C26: 10p; C_0402_1005Metric; MPN GRM1555C1H100JA01D
C27: 100n; C_0402_1005Metric; MPN GRM155R71C104KA88D
D1, D3, D5, D7, D9, D11, D13, D15: LED red; LED_0402_1005Metric; MPN APHHS1005SURCK
D2, D4, D6, D8, D10, D12, D14, D16: LED NIR; LED_0402_1005Metric; MPN APHHS1005F3C
PD1: Photodiode; Photodiode_4.8x2.5mm; MPN VEMD5510C
R1, R2, R3, R4, R5: 68R; R_0402_1005Metric; MPN RC0402FR-0768RL
R16: 470k; R_0402_1005Metric; MPN RC0402FR-07470KL
R17, R18: 100k; R_0402_1005Metric; MPN RC0402FR-07100KL

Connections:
CP1: D1.2 (A), D2.1 (K), D9.1 (K), D10.2 (A), D11.2 (A), D12.1 (K), R1.2
CP1_MCU: R1.1; also elsewhere on the board
CP2: D1.1 (K), D2.2 (A), D3.2 (A), D4.1 (K), D13.2 (A), D14.1 (K), R2.2
CP2_MCU: R2.1; also elsewhere on the board
CP3: D3.1 (K), D4.2 (A), D5.2 (A), D6.1 (K), D11.1 (K), D12.2 (A), D15.2 (A), D16.1 (K), R3.2
CP3_MCU: R3.1; also elsewhere on the board
CP4: D5.1 (K), D6.2 (A), D7.2 (A), D8.1 (K), D13.1 (K), D14.2 (A), R4.2
CP4_MCU: R4.1; also elsewhere on the board
CP5: D7.1 (K), D8.2 (A), D9.2 (A), D10.1 (K), D15.1 (K), D16.2 (A), R5.2
CP5_MCU: R5.1; also elsewhere on the board
GND: C27.2, R18.2; also elsewhere on the board
OPAMP_OUT: C26.2, R16.2; also elsewhere on the board
PD_K: C26.1, PD1.K, R16.1; also elsewhere on the board
V2V8: R17.1; also elsewhere on the board
VBIAS: C27.1, PD1.A, R17.2, R18.1; also elsewhere on the board

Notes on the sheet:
grain - 27 parts

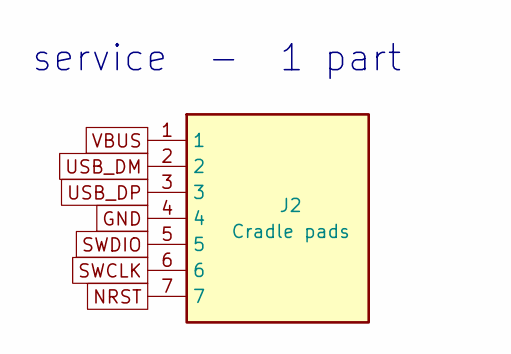
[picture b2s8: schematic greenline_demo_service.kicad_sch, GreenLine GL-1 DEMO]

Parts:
J2: Cradle pads; ContactRow_7x1.8mm_P2.54

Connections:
GND: J2.4; also elsewhere on the board
NRST: J2.7; also elsewhere on the board
SWCLK: J2.6; also elsewhere on the board
SWDIO: J2.5; also elsewhere on the board
USB_DM: J2.2; also elsewhere on the board
USB_DP: J2.3; also elsewhere on the board
VBUS: J2.1; also elsewhere on the board

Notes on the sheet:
service - 1 part
